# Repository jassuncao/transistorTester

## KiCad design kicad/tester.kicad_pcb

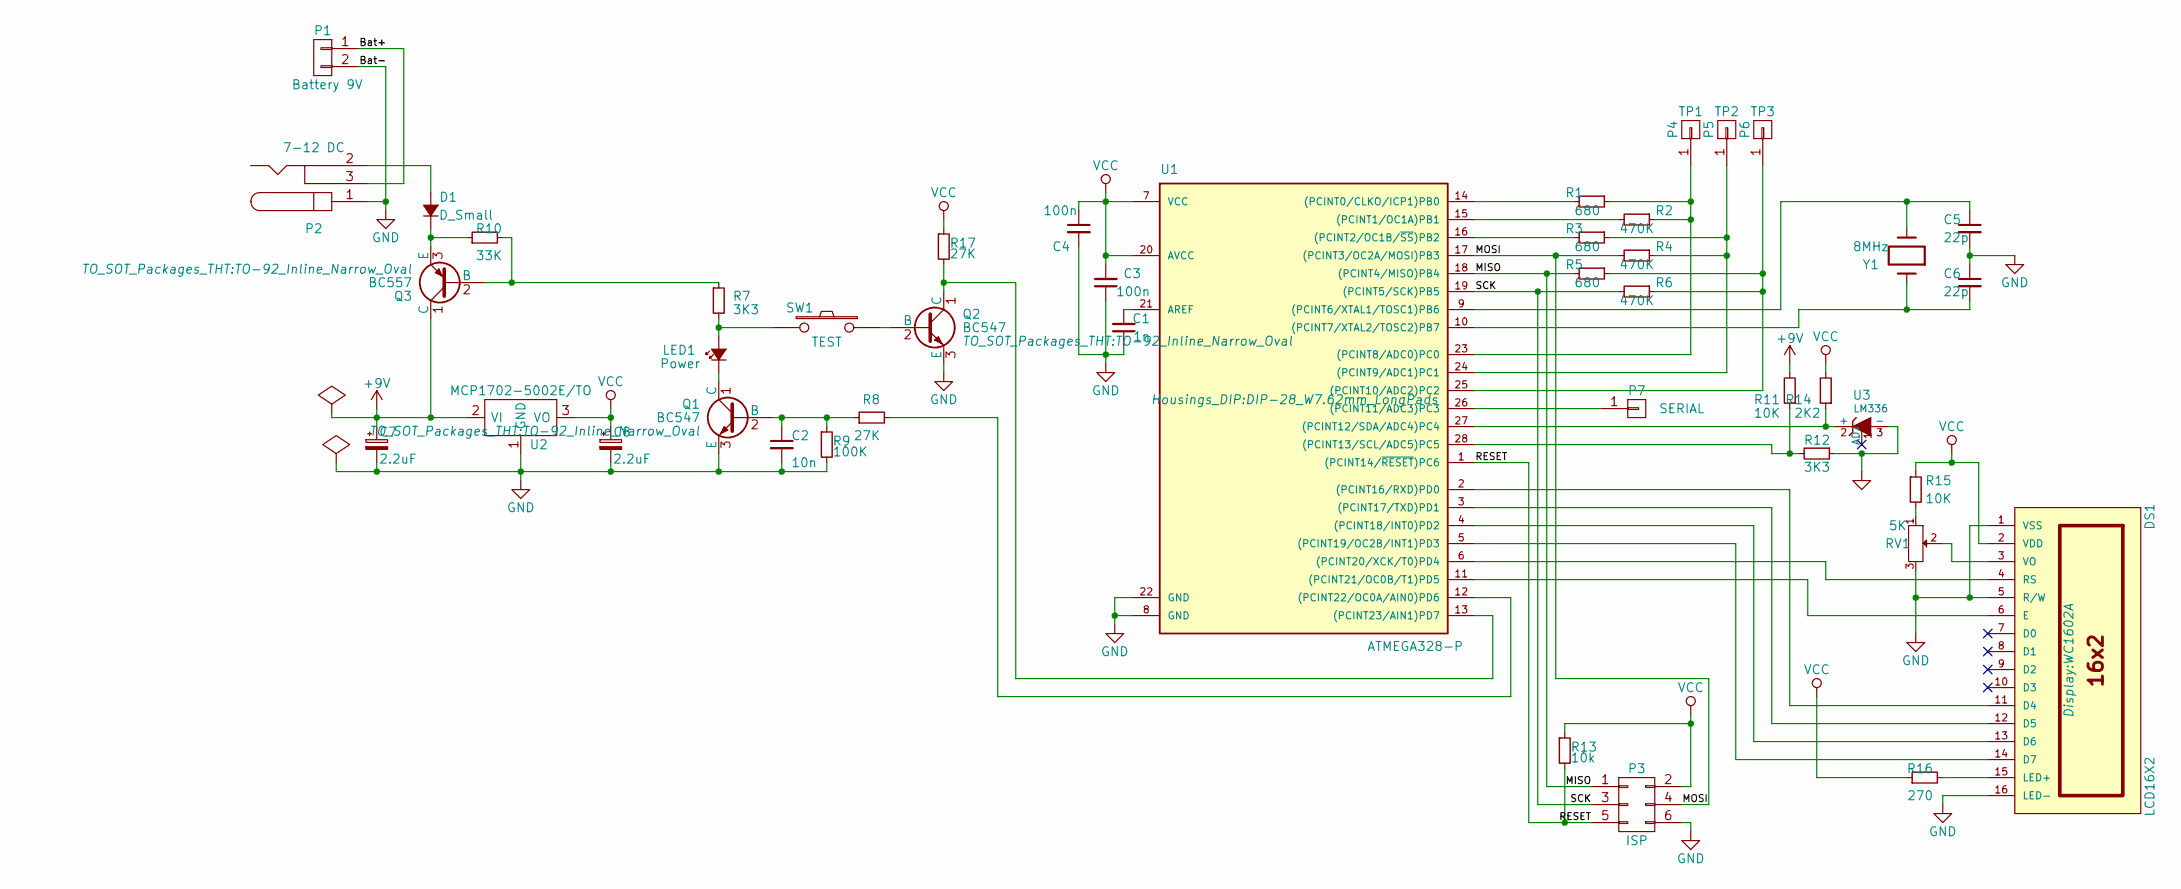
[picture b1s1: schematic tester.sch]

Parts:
C1: 1n; C_Disc_D3_P2.5
C2: 10n; C_Disc_D3_P2.5
C3, C4: 100n; C_Disc_D6_P5
C5, C6: 22p; C_Disc_D3_P2.5
C7, C8: 2.2uF; C_Radial_D6.3_L11.2_P2.5
D1: D_Small; Diode_DO-35_SOD27_Horizontal_RM10
DS1: LCD16X2; WC1602A
LED1: Power; LED-3MM
P1: Battery 9V; PINHEAD1-2
P2: 7-12 DC; BARREL_JACK
P3: ISP; Pin_Header_Straight_2x03
P4: TP1; SolderWirePad_single_1mmDrill
P5: TP2; SolderWirePad_single_1mmDrill
P6: TP3; SolderWirePad_single_1mmDrill
P7: SERIAL; SolderWirePad_single_1mmDrill
Q1, Q2: BC547; TO-92_Inline_Narrow_Oval
Q3: BC557; TO-92_Inline_Narrow_Oval
R1, R3, R5: 680; Resistor_Horizontal_RM10mm
R2, R4, R6: 470K; Resistor_Horizontal_RM10mm
R7, R12: 3K3; Resistor_Horizontal_RM10mm
R8, R17: 27K; Resistor_Horizontal_RM10mm
R9: 100K; Resistor_Horizontal_RM10mm
R10: 33K; Resistor_Horizontal_RM10mm
R11, R15: 10K; Resistor_Horizontal_RM10mm
R13: 10k; Resistor_Horizontal_RM10mm
R14: 2K2; Resistor_Horizontal_RM10mm
R16: 270; Resistor_Horizontal_RM10mm
RV1: 5K; Potentiometer_VishaySpectrol-Econtrim-Type36k
SW1: TEST; PINHEAD1-2
U1: ATMEGA328-P; DIP-28_W7.62mm_LongPads
U2: MCP1702-5002E/TO; TO-92_Inline_Narrow_Oval
U3: LM336; TO-92_Inline_Narrow_Oval
Y1: 8MHz; Crystal_HC49-U_Horizontal_Typ1

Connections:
+9V: C7.1, Q3.1 (C), R11.2, U2.2 (VI)
/Bat+: P1.1, P2.3
/MISO: P3.1, R5.2, U1.18 ((PCINT4/MISO)PB4)
/MOSI: P3.4, R4.2, U1.17 ((PCINT3/OC2A/MOSI)PB3)
/RESET: P3.5, R13.2, U1.1 ((PCINT14/~RESET~)PC6)
/SCK: P3.3, R6.2, U1.19 ((PCINT5/SCK)PB5)
GND: C1.1, C2.2, C3.1, C4.2, C5.2, C6.1, C7.2, C8.2, DS1.1 (VSS), DS1.5 (R/W), DS1.16 (LED-), P1.2, P2.1, P3.6, Q1.3 (E), Q2.3 (E), R9.2, R12.1, RV1.3, U1.8 (GND), U1.22 (GND), U2.1 (GND), U3.3 (-)
unnamed: C1.2, U1.21 (AREF)
unnamed: C2.1, Q1.2 (B), R8.1, R9.1
unnamed: C5.1, U1.9 ((PCINT6/XTAL1/TOSC1)PB6), Y1.2
unnamed: C6.2, U1.10 ((PCINT7/XTAL2/TOSC2)PB7), Y1.1
unnamed: D1.1 (K), Q3.3 (E), R10.1
unnamed: D1.2 (A), P2.2
unnamed: DS1.3 (VO), RV1.2
unnamed: DS1.4 (RS), U1.6 ((PCINT20/XCK/T0)PD4)
unnamed: DS1.6 (E), U1.11 ((PCINT21/OC0B/T1)PD5)
unnamed: DS1.11 (D4), U1.2 ((PCINT16/RXD)PD0)
unnamed: DS1.12 (D5), U1.3 ((PCINT17/TXD)PD1)
unnamed: DS1.13 (D6), U1.4 ((PCINT18/INT0)PD2)
unnamed: DS1.14 (D7), U1.5 ((PCINT19/OC2B/INT1)PD3)
unnamed: DS1.15 (LED+), R16.2
unnamed: LED1.1 (K), Q1.1 (C)
unnamed: LED1.2 (A), R7.2, SW1.2
unnamed: P4.1, R1.1, R2.1, U1.23 ((PCINT8/ADC0)PC0)
unnamed: P5.1, R3.1, R4.1, U1.24 ((PCINT9/ADC1)PC1)
unnamed: P6.1, R5.1, R6.1, U1.25 ((PCINT10/ADC2)PC2)
unnamed: P7.1, U1.26 ((PCINT11/ADC3)PC3)
unnamed: Q2.1 (C), R17.2, U1.13 ((PCINT23/AIN1)PD7)
unnamed: Q2.2 (B), SW1.1
unnamed: Q3.2 (B), R7.1, R10.2
unnamed: R1.2, U1.14 ((PCINT0/CLKO/ICP1)PB0)
unnamed: R2.2, U1.15 ((PCINT1/OC1A)PB1)
unnamed: R3.2, U1.16 ((PCINT2/OC1B/~SS~)PB2)
unnamed: R8.2, U1.12 ((PCINT22/OC0A/AIN0)PD6)
unnamed: R11.1, R12.2, U1.28 ((PCINT13/SCL/ADC5)PC5)
unnamed: R14.1, U1.27 ((PCINT12/SDA/ADC4)PC4), U3.2 (+)
unnamed: R15.2, RV1.1
VCC: C3.2, C4.1, C8.1, DS1.2 (VDD), P3.2, R13.1, R14.2, R15.1, R16.1, R17.1, U1.7 (VCC), U1.20 (AVCC), U2.3 (VO)

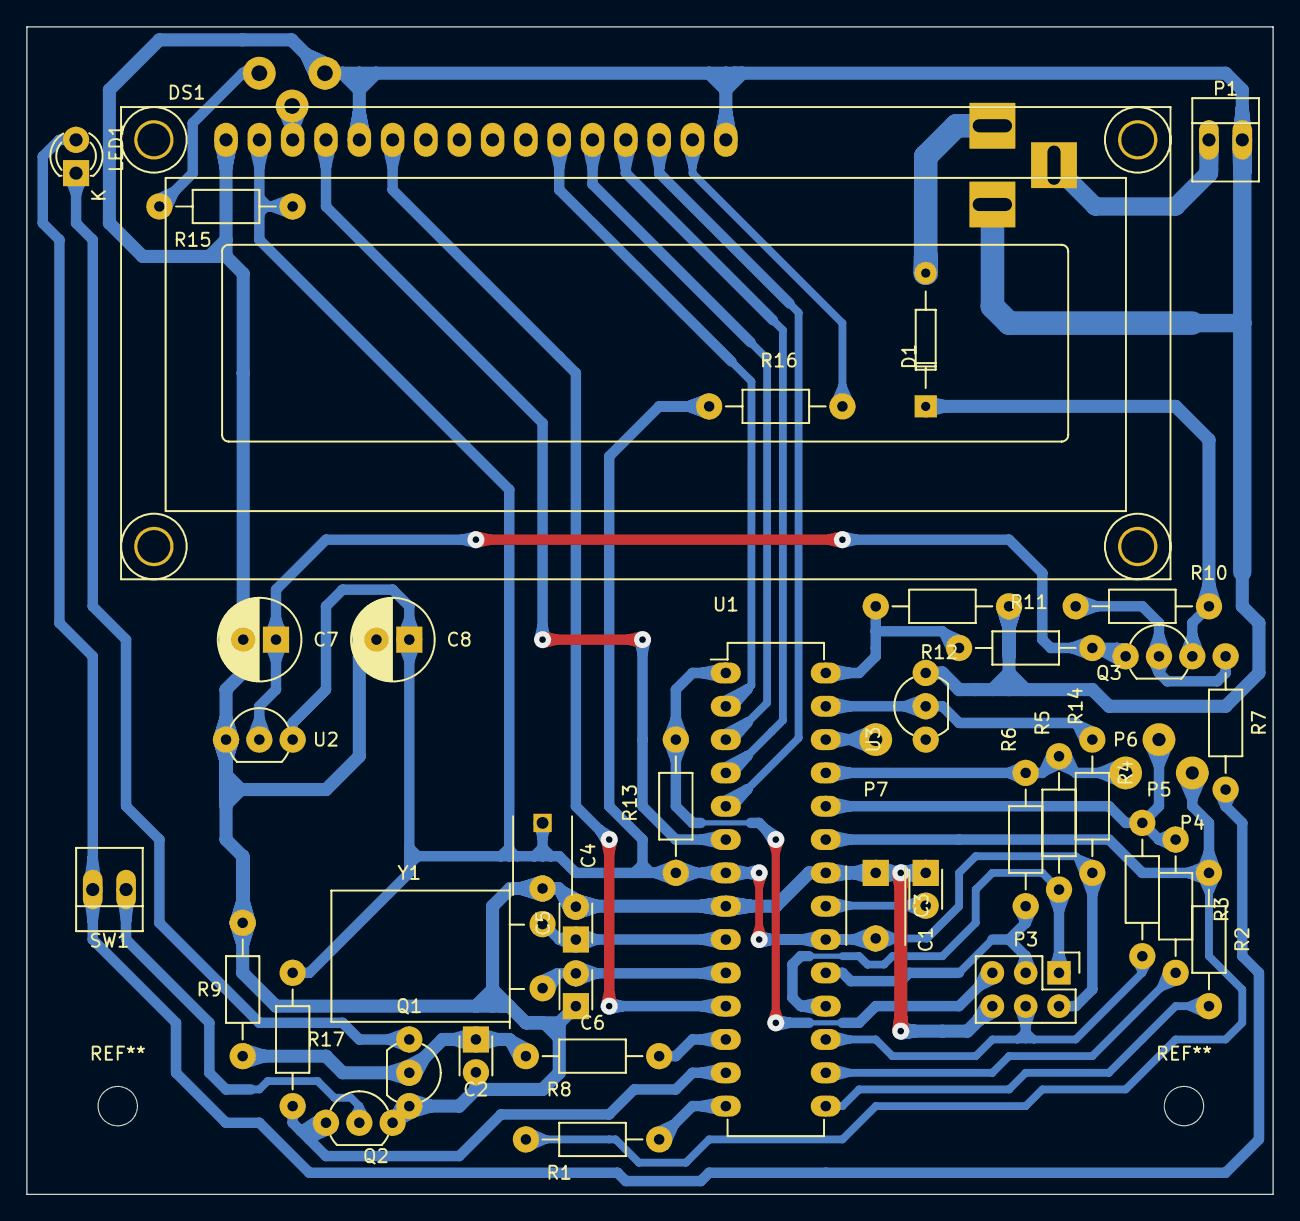
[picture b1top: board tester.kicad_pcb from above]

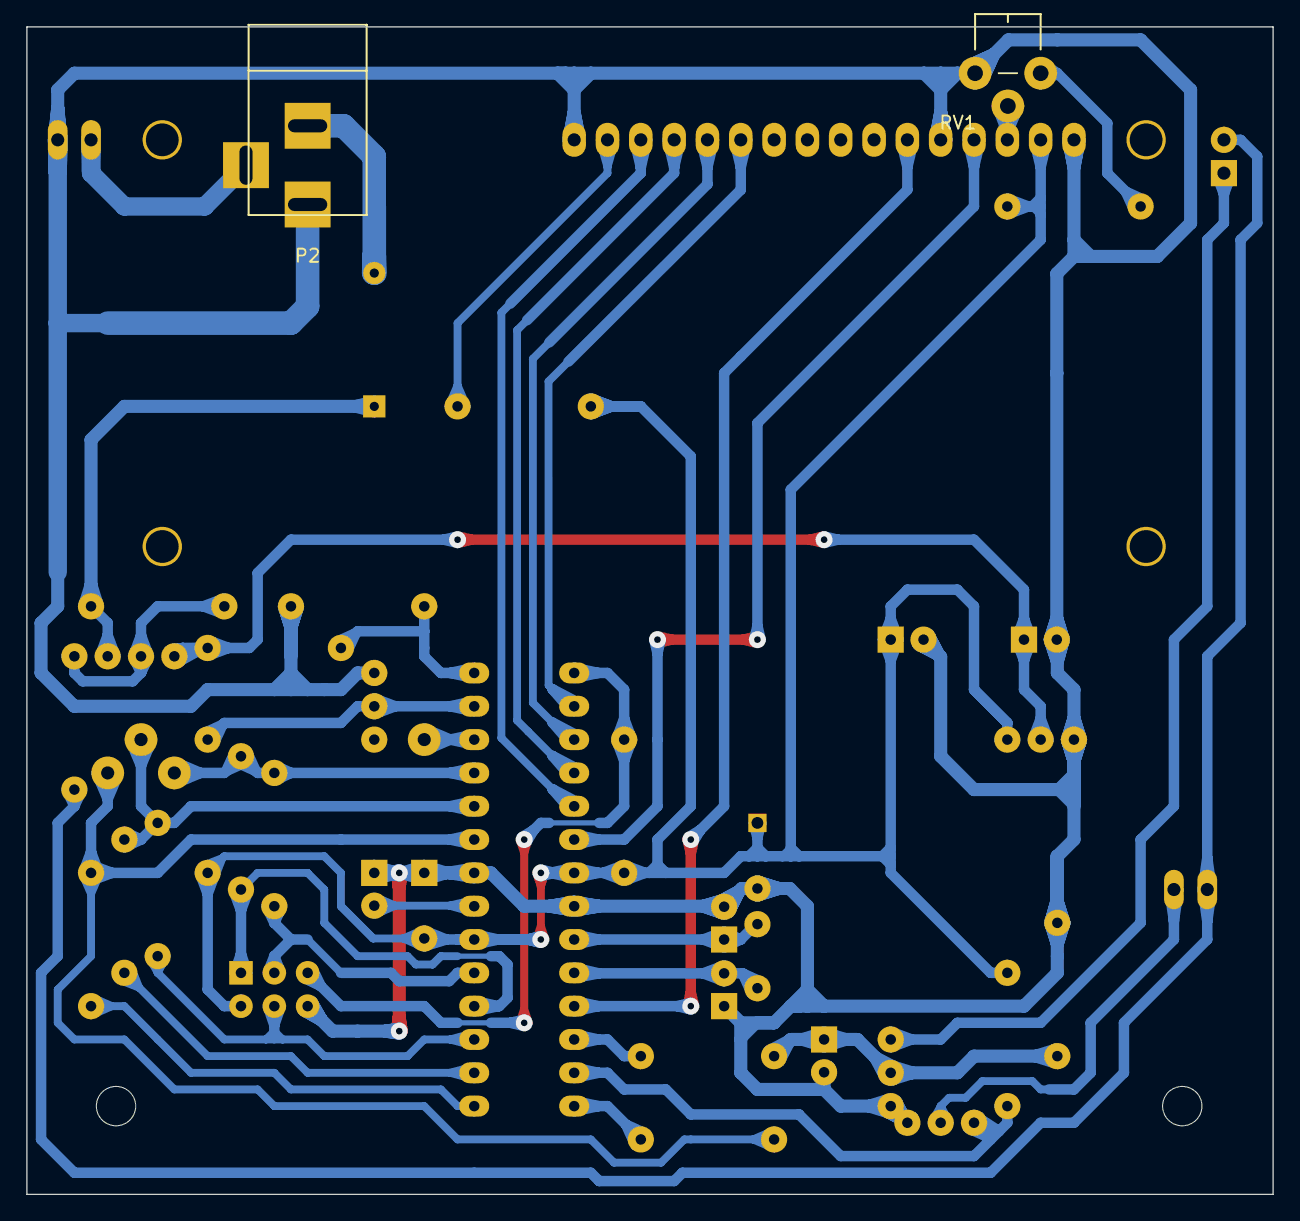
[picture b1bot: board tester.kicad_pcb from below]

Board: 2 copper layers, 95.0 x 89.0 mm, 44 parts (2 on the bottom side), 38 nets.

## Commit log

2016-09-26 Initial import
2016-09-28 * Schematic capture almost complete. Missing LCD section
2016-09-29 Schematic capture almost complete
2016-09-30 Schematic complete. Some refs des. incomplete
2016-11-26 Board routing almost done
2016-11-29 * Minor changes
2016-12-01 * Adds teardrop * Minor improvements
